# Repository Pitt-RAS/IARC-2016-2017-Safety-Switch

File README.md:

# IARC-2016-2017-Safety-Switch
IARC7 Safety Kill Switch for quad

This repository is part of the Pitt RAS effort for IARC Mission 7.  For an overview of the IARC competition as well as the team's efforts and technical approaches, check out our [team website](http://pittras.org/projects/IARC/), and in particular the [technical postmortem post for the project](http://pittras.org/projects/iarc/2018/08/10/update-iarc-technical-postmortem.html).

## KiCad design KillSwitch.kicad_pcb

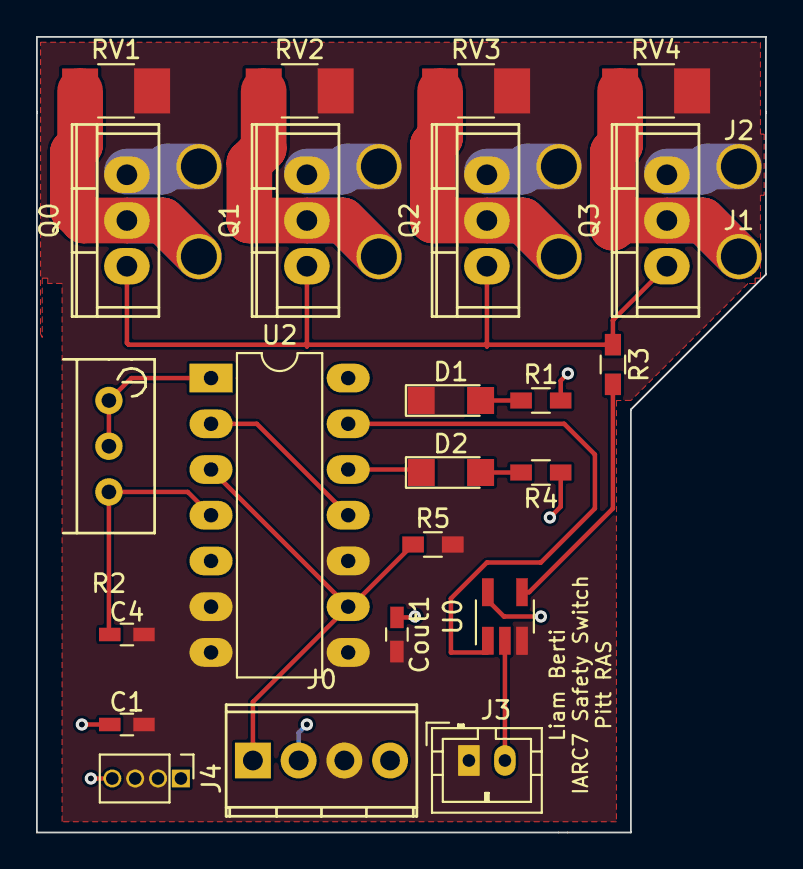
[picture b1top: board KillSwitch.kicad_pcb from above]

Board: 2 copper layers, 40.5 x 44.2 mm, 25 parts (0 on the bottom side), 17 nets.

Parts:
C1: 0.1uF; C_0603_HandSoldering
C4: 1.0uF; C_0603_HandSoldering
Cout1: 22uF; C_0603_HandSoldering
D1: Green LED; LED_1206
D2: Red LED; LED_1206
J0: Screw_Terminal_1x04; TerminalBlock_Pheonix_MPT-2.54mm_4pol
J1, J2: CONN_01X04; barrel_connector
J3: CONN_01X02; JST_PH_B2B-PH-K_02x2.00mm_Straight
J4: CONN_01X04; Socket_Strip_Straight_1x04_Pitch1.27mm
Q0, Q1, Q2, Q3: IRF1324PBF; TO-220
R1, R4: 475; R_0603_HandSoldering
R2: 5k; Potentiometer_Bourns_3296W_3-8Zoll_Inline_ScrewUp
R3: 500; R_0603_HandSoldering
R5: 10.0k; R_0603_HandSoldering
RV1, RV2, RV3, RV4: Varistor; R_1210_HandSoldering
U0: NC7SZ08; SOT-23-5_HandSoldering
U2: 4013; DIP-14_W7.62mm_LongPads

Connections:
+5V: C1.1, Cout1.1, J0.2, J4.4, R1.2, R4.1, U0.5, U2.5, U2.14
/AND1: U0.1, U2.13
/AND2: J3.2, U0.2
/GATE: Q0.1, Q1.1, Q2.1, Q3.1, R3.1
/PWM: J0.1, R5.1, U2.3, U2.9
Earth: C1.2, C4.2, Cout1.2, D1.1, J0.3, J1.1, J1.2, J1.3, J1.4, J3.1, J4.2, J4.3, Q0.3, Q1.3, Q2.3, Q3.3, R5.2, RV1.2, RV2.2, RV3.2, RV4.2, U0.3, U2.6, U2.7, U2.8, U2.10
unnamed: C4.1, R2.3, U2.4
unnamed: D1.2, R1.1
unnamed: D2.1, U2.12
unnamed: D2.2, R4.2
unnamed: J2.1, Q3.2, RV4.1
unnamed: J2.2, Q2.2, RV3.1
unnamed: J2.3, Q1.2, RV2.1
unnamed: J2.4, Q0.2, RV1.1
unnamed: R2.1, R2.2, U2.1
unnamed: R3.2, U0.4
unnamed: U2.2, U2.11

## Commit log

2017-04-13 added custom parts dir
2017-04-13 Added copper pads so barrel wires can be soldered on bottom
2017-04-14 Added standoff holes to pcb
2017-04-14 Added standoff holes to pcb FIX
2017-04-14 Fixed Motor holes
2017-06-05 new switch
2017-06-05 Added features
2017-06-05 Add varistors to DS
2017-06-06 Added gerber and drill files
2017-06-06 Add traces on bottom plane as well as top for high current
2017-06-06 Move gerbers and drill to their own file
2017-06-06 Update gerbers with new traces
